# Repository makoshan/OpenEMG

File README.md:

# OpenEMG

**简体中文** · [English](README.en.md) · **[官网 openemg.org](https://openemg.org/)**

OpenEMG 是一个 **16 通道开源肌电手环**项目。我们想用腕部的表面肌电信号识别手势。桌面软件可以查看各通道波形、录制动作和训练模型。

我们想做肌电界的 DeepSeek。电路、结构、固件和桌面软件全部开源，谁都可以照着做一块板，用自己的数据训练模型。

OpenEMG 由人和 AI 共同研发。项目还在早期，电路、代码和文档里难免有错。如果你发现问题，欢迎[提 issue](https://github.com/makoshan/OpenEMG/issues)。如果你改好了代码、电路，或测出了不同的结果，也欢迎[提交 PR](https://github.com/makoshan/OpenEMG/pulls)，让其他人能复用你的工作。

**本次下单的最终主板为 OpenEMG MAIN V1.0B（2026-11-24）。** 首件已下单，实物待验。下载主板 PCB、五页原理图、Gerber 和实际贴片 BOM，见[主板定版资料](hardware/main-v1.0b/)。

[当前状态与进展计划](#当前状态与进展计划) · [Gallery](#gallery) · [工作原理与调研](#工作原理) · [桌面工作台](#桌面工作台)

| 正面 · U9 外壳与双板 | 贴肤面 · 金属电极触点 |
|---|---|
|  |  |

外观沿用 R13 表带，贴肤面按双 30 针电极软板布局绘制。长带 24 个、短带 4 个、主机底部 4 个圆形采样触点，共组成 16 对差分输入。底部另有 2 个方形辅助触点。这套组合尚待实物试装。 [表带模型](hardware/enclosure-46x40/c08b-shell-r13-notch/) · [双 30 针电极软板](hardware/16ch-u9-dual30/strap-fpc-30p/)

**OpenEMG 还在早期研制阶段。** 2026 年 11 月 15 日定下的是打样用的 PCB。固件、桌面软件与板子的联调、手势识别都还在开发，16 通道整机尚未上机验证。

> [!IMPORTANT]
> **人工审核准备下单 vs AI 生成未下单（硬件状态声明）**
> - **16 通道 `v0.01` 双板（人工工程师设计并逐脚审核通过 · 准备下单打样）**：[`hardware/16ch-afe-hirose-1mm-1nf/`](hardware/16ch-afe-hirose-1mm-1nf/) 中的 6 层主控板 `C08B-U9` 与 4 层采集板 `AFE-30P`（含 32 颗 `ESD401DPYR` 输入保护管、146 个贴片位号）由人工硬件工程师完成原理图与 PCB 布局布线，并对照 TI `ADS1298` 数据手册与 `SBAU171D` 评估板指南完成逐脚复核、DRC 与贴片极性核对，准备下单打样。
> - **其余衍生板卡、柔性软板与外壳（AI 生成设计 · 尚未人工审核 · 尚未下单）**：仓库内的 **2 通道 `ADS1292` 六触点板**、**8 通道 `D20-8CH` 腕带板**、**16 通道双 34 针（`D20/R4U6`）与广濑 `22 pF` 穿戴派生版（`16ch-u9-dual30`）**、**讯普 `2.0 mm` 对照版**、**全系柔性电极软板（FPC）** 以及 **全系 3D 打印外壳模型** 均由 AI 生成，尚未经过人工工程师逐板审核，也**尚未下单打样**（仅历史 8 路台架开发板 [`V12-R01`](hardware/8ch-ads1298/r01-bench/) 做过离体短接实板测试）。如需复刻 AI 生成的板卡，请务必在投产前自行人工复核原理图、封装手性与安全间距。

6 层主控板通过 20 针排线连接 4 层采集板。采集板用两颗 ADS1298，设计为 16 路差分输入。[打开人工审核双板工程与制造文件](hardware/16ch-afe-hirose-1mm-1nf/)

## Gallery

### PCB · 主控与采集板

**v0.01 的 PCB 设计已完成，下一步是打板、贴片和上电测试。** 采集板新增 32 颗输入保护管（D101–D132），贴片 BOM 和坐标表共 146 个位号。

| 板卡 | 正面 | 背面 |
|---|---|---|
| C08B-U9 主控板 |  |  |
| 16 通道采集板 |  |  |

图由同版 Gerber 生成。右列按翻到板背后的方向显示。[双板工程与制造文件](hardware/16ch-afe-hirose-1mm-1nf/) · [主控板元件正视图](hardware/renders/v001-mcu-front.png) · [采集板元件正视图](hardware/renders/v001-afe-front.png)

### 结构与装配

| v0.01 双板叠放 · 主控在上、采集在下 | U9 壳体与 v0.01 双板 · 分层视图 |
|---|---|
|  |  |

装配图按 v0.01 制造文件绘制，采用 0.8 mm 裸板。右图拉开了层间距，省略了元件、排线和电池。实物还没试装。[U9 外壳模型](hardware/16ch-u9-dual30/enclosure-u9-watch/) · [历代结构与表带图集](hardware/renders/)

### 走线与原理图

| C08B-U9 主控板 · 6 层铜箔 | 16 通道采集板 · 4 层铜箔 |
|---|---|
|  |  |

从左到右、从上到下依次是顶层、内层和底层。各层都从板顶看，方便对照走线和过孔。[主控 Gerber 与钻孔](hardware/16ch-afe-hirose-1mm-1nf/Gerber_C08B-U9_v0.01.zip) · [采集板 Gerber 与钻孔](hardware/16ch-afe-hirose-1mm-1nf/Gerber_AFE-30P.zip)

**[下载九页矢量原理图](hardware/16ch-afe-hirose-1mm-1nf/views/schematic.pdf)**。第 1 页是整机框图，第 2 页是电源树。第 3–7 页是主控板的供电、蓝牙、USB、板间接口与采样主控，第 8–9 页是采集板的模拟电源、采集芯片、电极接口与输入滤波。PDF 可放大和搜索位号；修改或联调电路请打开[嘉立创 EDA 专业版双板源工程](hardware/16ch-afe-hirose-1mm-1nf/OpenEMG_v0.01_DualBoard.epro2)或 [KiCad 8 原生双板与九页原理图工程](hardware/16ch-afe-hirose-1mm-1nf/kicad/)。

| 复刻资料 | 主控板 | 采集板 |
|---|---|---|
| 物料清单（BOM） | [主控 BOM](hardware/16ch-u9-dual30/fab-mcu-u9/jlc_smt_bom.csv) | [采集 BOM](hardware/16ch-afe-hirose-1mm-1nf/jlc_smt_bom.csv) |
| 贴片坐标（CPL） | [主控坐标](hardware/16ch-u9-dual30/fab-mcu-u9/jlc_smt_cpl.csv) | [采集坐标](hardware/16ch-afe-hirose-1mm-1nf/jlc_smt_cpl.csv) |

板厚、盘中孔工艺、钢网和底面贴装方向见[同版制造说明](hardware/16ch-afe-hirose-1mm-1nf/)。本版采集板用于离体台架，通电前请阅读[测试与佩戴边界](SAFETY.md)。

## 工作原理

捏指时，肌肉活动会让皮肤表面产生微小的电压变化。手环的每个通道测一对电极之间的电压差。电极位置不同，同一次捏指在各通道上录到的波形也不同。桌面软件把波形和动作标签一起保存，供模型学习区分放松、捏指等动作。

[查看同版九页原理图](hardware/16ch-afe-hirose-1mm-1nf/views/schematic.pdf)

摘下再戴，电极位置和松紧都会变。我们读过的一项四通道实验，在握拳、张手、屈腕和伸腕测试中判对了 152/160 次（95%），但论文没说明测试前是否重新佩戴，现有材料也不足以原样复现。[阅读项目调研节选与论文出处](research/wrist-semg.md)

结合文献复核与前期 8 路台架板（[`V12-R01`](hardware/8ch-ads1298/r01-bench/)）实测，定版电路与软件采用以下设计约束：

| 调研与实测维度 | 关键数据与来源 | 在 OpenEMG v0.01 与工作台中的落地 |
|---|---|---|
| **参考偏置与底噪** | `V12-R01` 实板短接输入底噪 **`2.8 µV`**，连续 10 分钟 **`1,187,774` 帧零丢包**；悬空不接参考电极上臂时 50 Hz 共模飙至 `10 mV` 饱和 | 盒底设独立 `BIAS / REF` 辅助触点，由 `U1` 单源经 `392 kΩ` 驱动偏置（`U2` 偏置输出悬空防双运放互顶），录制前先过 **5 秒静息信号体检**（`p95 > 150 µV` 阻断、`50 Hz` 能量占比 `> 40%` 提示重贴参考电极） |
| **双芯片同步与采样率** | 对照 ETH Zurich BioGAP-Ultra 双 `ADS1298` 架构与腕部 sEMG 有效频带（`20–450 Hz`） | 两颗 `ADS1298` 共用同一颗 `2.048 MHz` 有源晶振消除帧间漂移，硬件采样率定为 **`1000 SPS`**（兼容 `2000 SPS` 商用腕带回放与对比） |
| **跨佩戴特征与分类器** | 单次佩戴内准确率极易虚高；逐通道 z-score 标准化会抹掉空间幅值比，换位置重戴后性能骤降 | 禁用单通道标准化；提取 **`250 ms` 窗五频带对数功率（`bands5`：`20–45`、`55–95`、`105–145`、`155–245`、`255–445 Hz`）+ 收缩线性判别（Shrinkage LDA）**，桌面端强制按独立佩戴编号做**跨佩戴留一验证** |
| **人体供电互锁** | 市电 USB 直连存在故障漏电风险 | 主控板内建硬件互锁（检测 `VBUS` 自动拉高 `AFE_OE_N` 切断采集模拟电），`JP701` 默认空贴；桌面软件对未完成实物安全验收的 `c08b-16ch / 8ch / 2ch` 保持默认录制锁关闭（`record: false`） |

## 当前状态与进展计划

**2026-11-15 · 现在做到哪了**　16 通道 v0.01 的双板设计已定，工程、原理图、Gerber 和贴片文件已公开。固件通过了主机端测试，桌面工作台能演示 16 路波形。**这版整机还没有实测数据。最近的目标是让首板在台架上连续采到 16 路已知信号。**

#### 首板回来前

| 工作 | 还要做什么 |
|---|---|
| 打板与贴片 | 用 11 月 15 日定版包打样。核对板厚、盘中孔和钢网，在贴装预览里逐面检查两颗 ADS1298、三只排线座和 32 颗保护管。 |
| 固件适配 | [`c08b-bringup`](firmware/c08b-bringup/) 与 [`c08b-stream`](firmware/c08b-stream/) 已对照 `v0.01` 双板网表完成适配（双片独立 `INT_TEST=1` 测试源、`Pin 62 RLDIN=+2.5 V` 禁置 `RLD_MEAS/MUX=010`、`Pin 60 RLDREF=AGND` 禁置 `RLDREF_INT`，支持经蓝牙或 USB 接收器在线切换 `500/1000/2000 SPS` 及安全读写校验 `ADS1298` 寄存器，见[板间与传输协议说明](firmware/transport-protocol.md)），待回板后实机烧录验证。 |
| 测试准备 | 准备 20 针排线、转接线和离体信号源。把每个输入脚对应到桌面的 CH1–CH16，列好短接、已知信号和断流三组测试。 |

#### 样板到手后：先在台架测

| 工作 | 要拿到的结果 |
|---|---|
| 来板与供电 | 核对贴片方向、排线两端的 1 脚和通断。记录数字电源、正负模拟电源、基准电压、启动时序和纹波；验证 USB 插入时采集供电互锁。 |
| 双板通信 | 分别读回两颗 ADS1298 的 ID 和寄存器，观察各自的数据就绪信号，核对两组八路数据的顺序。 |
| 16 路模拟采集 | 先短接输入测各路底噪，再逐路注入已知信号。记录增益、极性、工频干扰和相邻通道串扰；用模拟负载检查偏置输出。 |
| 无线传输与桌面录制 | 真机连续传输，统计采样率、丢帧和延迟。用桌面端看波形、打标签、保存、关闭再回放；断连后检查文件是否完整、间断是否可见。2、8 通道另做兼容回归。 |
| 外壳、软板与电池 | 试装双板和电芯，实插 20 针板间排线和两条 30 针软尾。检查锁扣能否操作、合盖是否夹线，再测采集功耗、温升和续航。 |

#### 台架通过后：再做佩戴与手势验证

| 工作 | 怎样判断进展 |
|---|---|
| 佩戴前检查 | 核对贴肤触点、限流路径、电池供电与充电互锁，完成佩戴安全复核，再安排佩戴采集。[安全说明](SAFETY.md) |
| 电极接触与数据 | 记录佩戴位置和松紧，比较静息、动作、摘下重戴后的各路信号。保留动作标签和佩戴编号，找出容易失去接触的通道。 |
| 手势识别 | 先做放松、唤起和四向滑动六类。用一次佩戴训练，另一次佩戴测试；分别记录各类识别结果、响应时间和静息误触发。 |
| 开源复现 | 补齐装配照片、固件版本、桌面连接步骤和首板测试记录。让另一位开发者按公开文件从装配走到录制，记录卡在哪一步。 |

### 桌面工作台（支持 16 / 8 / 2 通道）

桌面工作台现已统一支持 **16 通道（OpenEMG 双 `ADS1298` · `1000 Hz`）**、**8 通道（唯理腕带 `2000 Hz` / OpenEMG 单 `ADS1298` `1000 Hz`）** 与 **2 通道（OpenEMG `ADS1292` · `1000 Hz`）**，顶部设备栏一键切换后自动匹配通道数、采样率、环形电极图、工程隔离目录与特征训练流水线。界面采用暖米色手帐实验台配色，录制前先过 5 秒静息信号体检（检查链全频段查 `50 Hz` 工频，显示链 `50 Hz` 陷波 + `20–450 Hz` 带通），内置跨佩戴留一评估与 3D 手势游戏《掌中天劫》。[打开软件目录与运行说明](app/)

| 16 通道肌电工作室（双 `ADS1298` · `16 CH · 1000 Hz`） | 8 通道校准采集中（满高八路滚动波形 · `8 CH · 2000 Hz`） |
|---|---|
|  |  |
| **2 通道入门工作台（`ADS1292` · `2 CH · 1000 Hz`）** | **跨佩戴评估剧场（重戴留一验证 `93%` + 学习曲线 + 聚类散点）** |
|  |  |
| **实时识别仪表盘（`0.65` 置信红线 + 放松底噪门控）** | **内置 3D 肌电实战游戏《掌中天劫》** |
|  |  |

图中 16 通道与 2 通道界面使用合成台架信号演示；在对应实板通过台架与佩戴安全验收前，软件默认保持硬件录制锁关闭（`record: false`）。

### 各版本工程与实测记录

目前优先打样并验证**人工审核通过的 16 通道 `v0.01` 双板**；其余 AI 生成的 16 / 8 / 2 通道衍生板、软板与外壳均尚未下单，进度与状态列在下表。

| 通道 | 硬件工程 | 固件 | 3D 外观（AI 生成 · 未下单） | 审核与下单实测状态 |
|---|---|---|---|---|
| **16 通道** | **[v0.01 双板与广濑 1 nF（人工审核）](hardware/16ch-afe-hirose-1mm-1nf/)** · **[A5＋B1 双层表带软板（已下单待试装）](hardware/16ch-afe-hirose-1mm-1nf/strap-fpc-a5b1/)** · [广濑 22 pF 穿戴版（AI）](hardware/16ch-u9-dual30/) · [讯普双 30 针（AI）](hardware/16ch-afe-xunpu-2mm-1nf/) · [双 34 针（AI）](hardware/16ch-c08b-round/) | [主控自检](firmware/c08b-bringup/) · [双 ADS1298 采集](firmware/c08b-stream/) | **[25 mm R3 外壳与 TPU 表带（含六孔修订底盖，已下单待试装）](hardware/16ch-afe-hirose-1mm-1nf/enclosure-25mm-r3/)** · [U9 广濑版手表壳](hardware/16ch-u9-dual30/enclosure-u9-watch/) · [双 30 针四层软板](hardware/16ch-u9-dual30/strap-fpc-30p/) | **`v0.01` 双板已由人工工程师逐脚审核通过；配套 `strap-fpc-a5b1` 双层软板与 `25 mm R3` 外壳/表带已投单打样**，待回件验证 16 路采集与断电试装。其余派生版尚未下单（讯普版另有[偏置待确认项](hardware/16ch-afe-xunpu-2mm-1nf/#待工程师确认)）。 |
| **8 通道** | [D20-8CH 腕带板（AI）](hardware/8ch-ads1298/afe-d20-8ch/) · [11 页原理图 PDF](hardware/8ch-ads1298/afe-d20-8ch/views/schematic.pdf) · [34P/20P 逐针核对表](hardware/8ch-ads1298/afe-d20-8ch/PINOUT-AND-REVIEW.md) · [R01 台架板（已实测）](hardware/8ch-ads1298/r01-bench/) | [腕带采集](firmware/c08b-stream/) · [R01 蓝牙采集](hardware/8ch-ads1298/r01-bench/firmware-f05-ble-dout/) | [R12 外壳](hardware/enclosure-46x40/c08b-shell-r12/) · [D2-8CH 电极软板](hardware/8ch-ads1298/strap-fpc-d2-8ch/) | `R01` 历史台架实板短接输入采集 10 分钟，`1,187,774` 帧序号连续、底噪 `2.8 µV`。`D20-8CH` 腕带板已整理 11 页全套原理图、34P/20P 逐针表与排线朝向图，**待人工工程师独立审板**，尚未下单。 |
| **2 通道** | [ADS1292 六触点板（AI）](hardware/2ch-ads1292/) · [双肩外接线 S1 与整板 STEP](hardware/2ch-shoulder-s1/) · [3 页原理图 PDF](hardware/2ch-ads1292/views/schematic.pdf) · [六触点极性核对表](hardware/2ch-ads1292/PINOUT-AND-REVIEW.md) | [XIAO 蓝牙采集](firmware/xiao-ads1292-2ch/) | [R7 六触点外壳](hardware/enclosure-46x40/ads1292-shell-r7/) | 已整理 3 页原理图、六触点贴肤翻面/元件面极性对照与 8 测点表（自动 DRC 与逐脚对板已过），**待人工工程师独立审板**，尚未下单。 |

## 开始使用

[官网 openemg.org](https://openemg.org/) · [桌面工作台](app/) · [软件与开发环境](firmware/software.md) · [板间与传输协议](firmware/transport-protocol.md) · [硬件与制造文件索引](hardware/README.md) · [通电与佩戴安全须知](SAFETY.md)

[软件许可 MIT](LICENSE) · [硬件许可 CERN-OHL-S-2.0](LICENSE-HARDWARE) · [第三方声明](THIRD_PARTY_NOTICES.md)

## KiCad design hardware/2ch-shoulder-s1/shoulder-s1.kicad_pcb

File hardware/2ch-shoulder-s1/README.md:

# S1 双肩肌电采集板

S1 是从双通道 R10派生的台架候选。使用 ADS1292 与原有 P44e + XIAO nRF52840 Sense。43.1 × 36.5 × 0.8 mm 四层采集板底面有两只电极线插座。工程入口为 [shoulder-s1.kicad_pro](shoulder-s1.kicad_pro)。静态设计已完成，尚未打样、上电或贴肤。

[下载整板 STEP](shoulder-s1.step) · [KiCad 原理图](shoulder-s1.kicad_sch) · [接口针序与出线图](board-bottom.png) · [模型来源与许可](MODELS.md)

## 两束电极线

| 插座 | 出线方向（从元件面看） | 1 脚 | 2 脚 | 3 脚 |
|---|---|---|---|---|
| J3 LEFT | 西边 | 左肩 CH1+ | 左辅助参考 | 左肩 CH1− |
| J4 RIGHT | 东边 | 右肩 CH2+ | 右辅助参考 | 右肩 CH2− |

每束使用一只 JST PHR-3 线端胶壳配 S3B-PH-SM4-TB 板端侧插座。线端按壳体的 1 脚标记核序，通断档逐芯核对。每束两根测量线在同侧成对走线，第 2 脚单独引出。两根辅助参考分别经过 620 kΩ，在板内汇合后经 300 kΩ 接 RLDOUT；它们由同一偏置驱动，均不可接屏蔽或电源地。四个信号输入各经两颗 300 kΩ 和中间节点的 ESD 保护。两只插座的 MP 是机械焊脚，每只座的两只 MP 在板上相连并与信号、电源地隔开。[JST PH 系列图纸](https://www.jst-mfg.com/product/pdf/eng/ePH.pdf)

J3 与 J4 的插拔轴线分别朝外，PCB 面内出口各自面向就近板边。两座均增加板底高度。肩颈壳需要双侧开口和两处夹持绝缘外皮的线夹，导线拉力应由壳体承受。既有腕带底盖开的是六个干电极孔，不能据此认定新插头能穿壳。首件需核插头、线夹、完整插拔行程及右侧上下两层 JST 线束与 J2 排线的共存。板底插座可手焊用于首件。

## 台架验收设计

下表为建议的原型验收条件，全部未实测。使用模拟负载和隔离差分信号源，记录实际线长、输入幅值、增益与原始帧。上电前核回路和电池供电时序；保留 R32 / Q1 的 USB 关断互锁及固件硬件锁。未确认供电、互锁及限流前，保持锁定。

| 测项 | 方法 | 建议通过条件 |
|---|---|---|
| 线束与保护 | 断电，从每根线远端量到板端针脚。核 4 个测量输入各到第一、第二级电阻末端，参考线到 RLDOUT。 | 线序同上表，输入约 300 / 600 kΩ，参考各约 920 kΩ。检查压接和绝缘。 |
| 通道与频响 | 正常双差分输入模式，先给左路、再给右路，从线束远端注入等幅正弦，另一通道接匹配的无信号模拟负载。每路扫 20、50、100、250、450 Hz。禁用显示端滤波，用原始 SPI 采样比较幅值。 | 4 kHz 为首选档。两路单独核算相对 100 Hz 的增益，各频点在 ±3 dB 内。记录另一通道同频响应和底噪，建议串扰 ≤ −40 dB。 |
| 同步和掉样 | 分别以 2 kHz、4 kHz 连续采 60 秒，同步比对 DRDY 边沿、两通道原始帧和溢出计数。 | 每个 DRDY 对应一个含两路数据的帧。按实测时钟核采样频率，完整记录窗口内无跳帧、无溢出。分别记录 SPI 与主机收包结果。 |
| 外接线与互锁 | 接上预定长度线束，测双路输入短接底噪、工频拾取及 RLD 是否振荡。用模拟负载验证 USB 插入后 TP8 拉低并停止转换；再用断电样件检查壳体夹线和插拔。 | 留存波形、互锁电平、端口及线束照片。人体试用另行做安全复核。 |

芯片的 2 / 4 kSPS 档 −3 dB 带宽分别为 524 / 1048 Hz。板级频响还受输入电路与线束影响。[TI 数据手册](https://www.ti.com/lit/ds/symlink/ads1292.pdf)

## 复核

在本目录用 KiCad 10.0.6 和 Python 3 运行 `python3 verify.py`。它从 S1 原理图重新导出网表，与从 R10 原理图导出的固定对照表 `r10-pins.csv` 比较，核对两组线序、其余 R10 引脚和关键保护件的标称值，注入右肩反接反例，再检查 ERC、重铺铜 DRC、未连接和图板一致性。工程带有 0.45 mm 无限流输入铜到电源和数字网络的间距规则。外壳、实际线缆和寄生参数仍须实测。

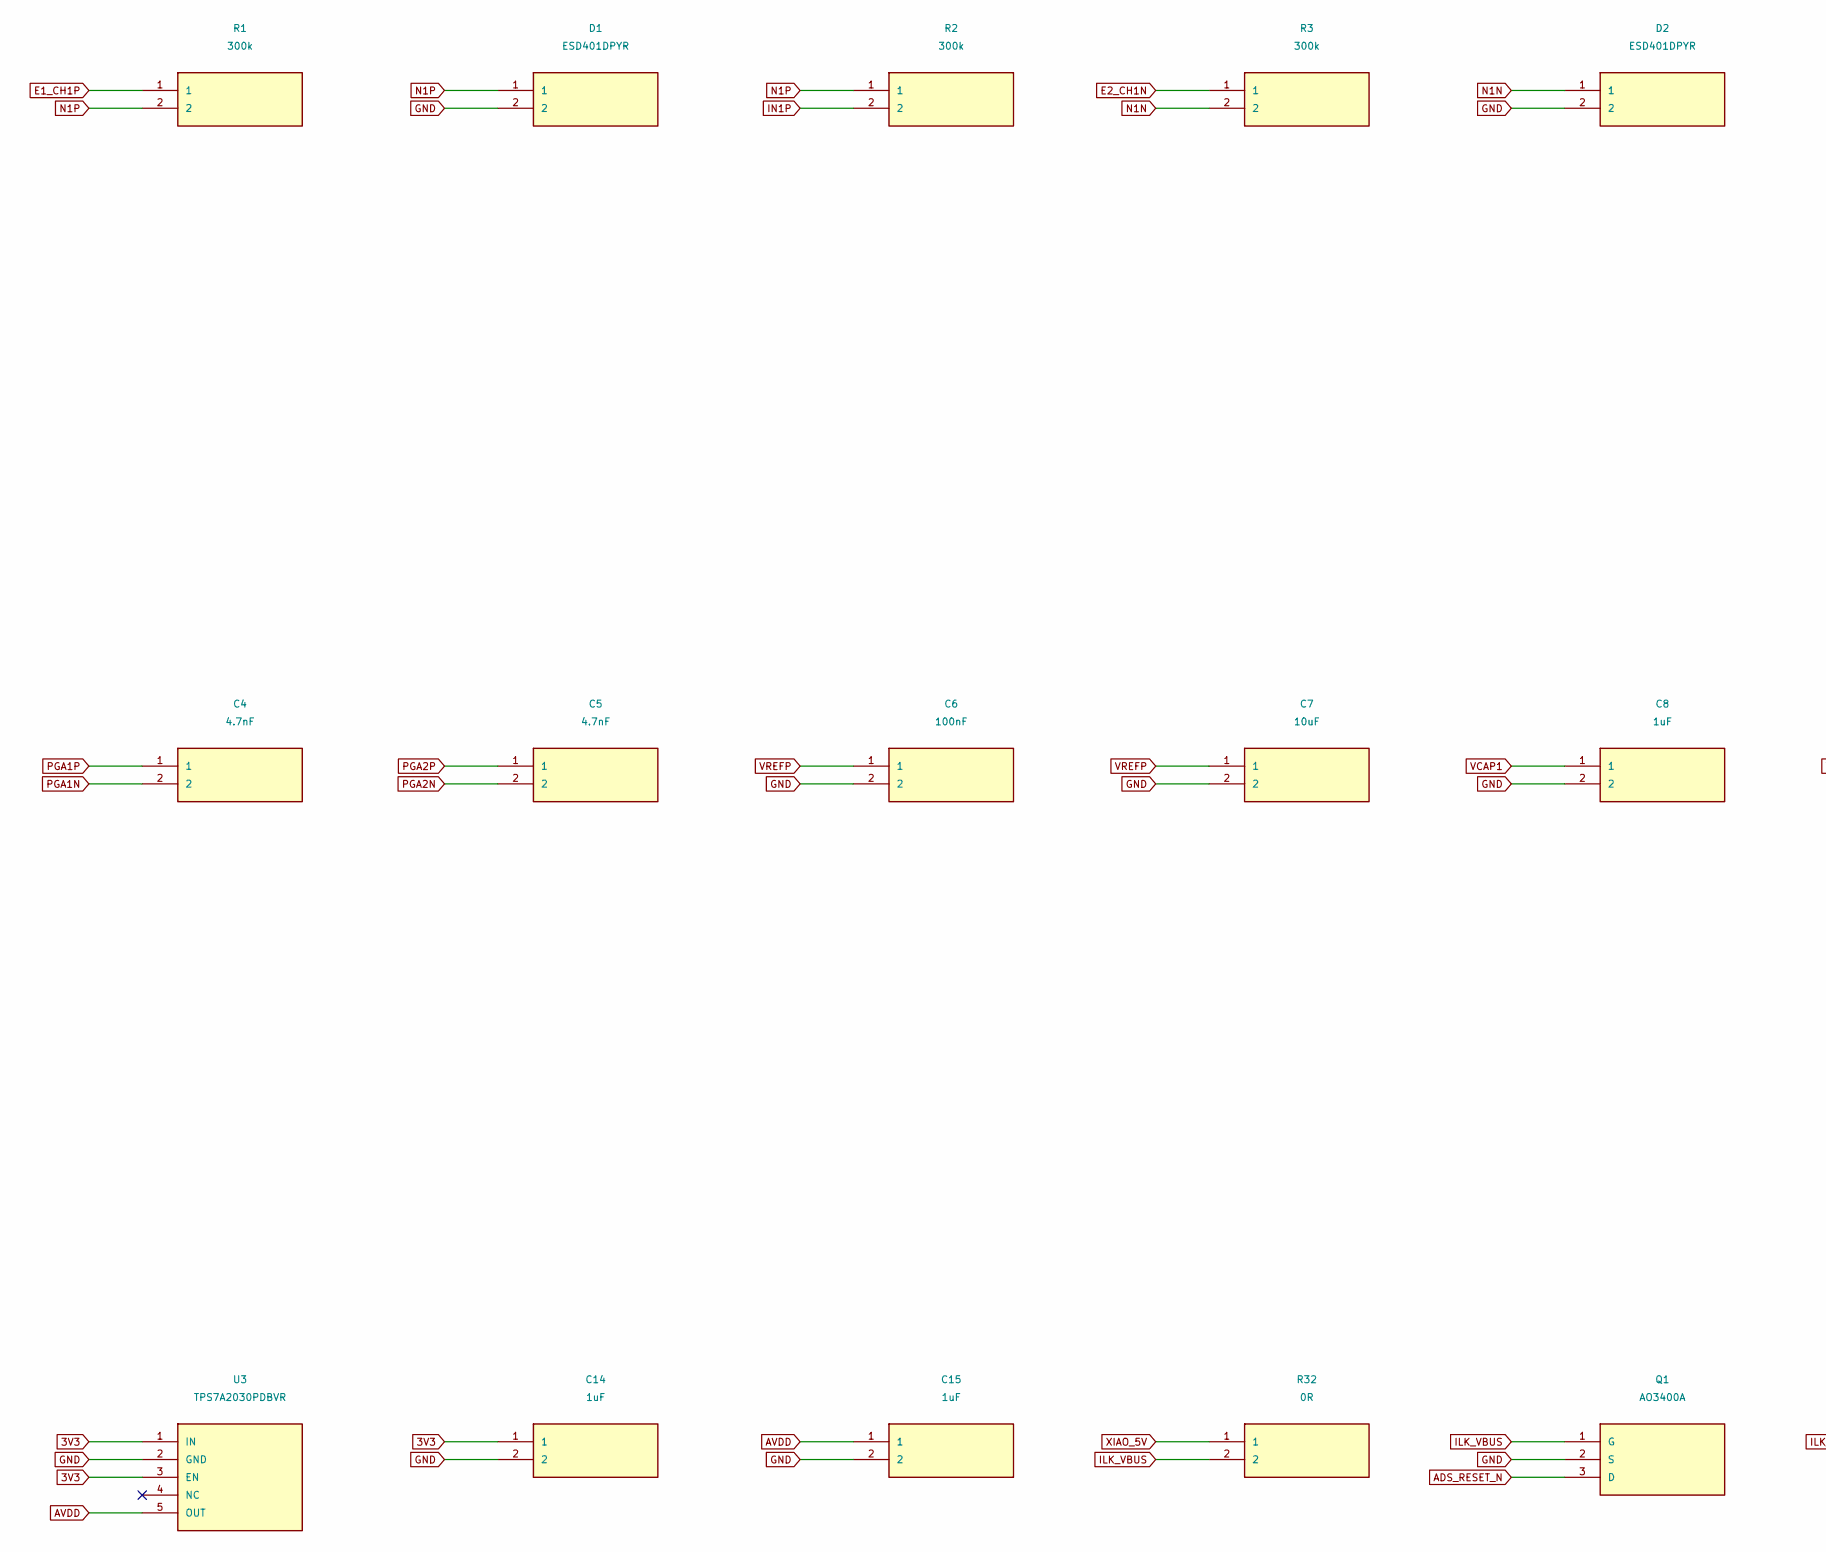
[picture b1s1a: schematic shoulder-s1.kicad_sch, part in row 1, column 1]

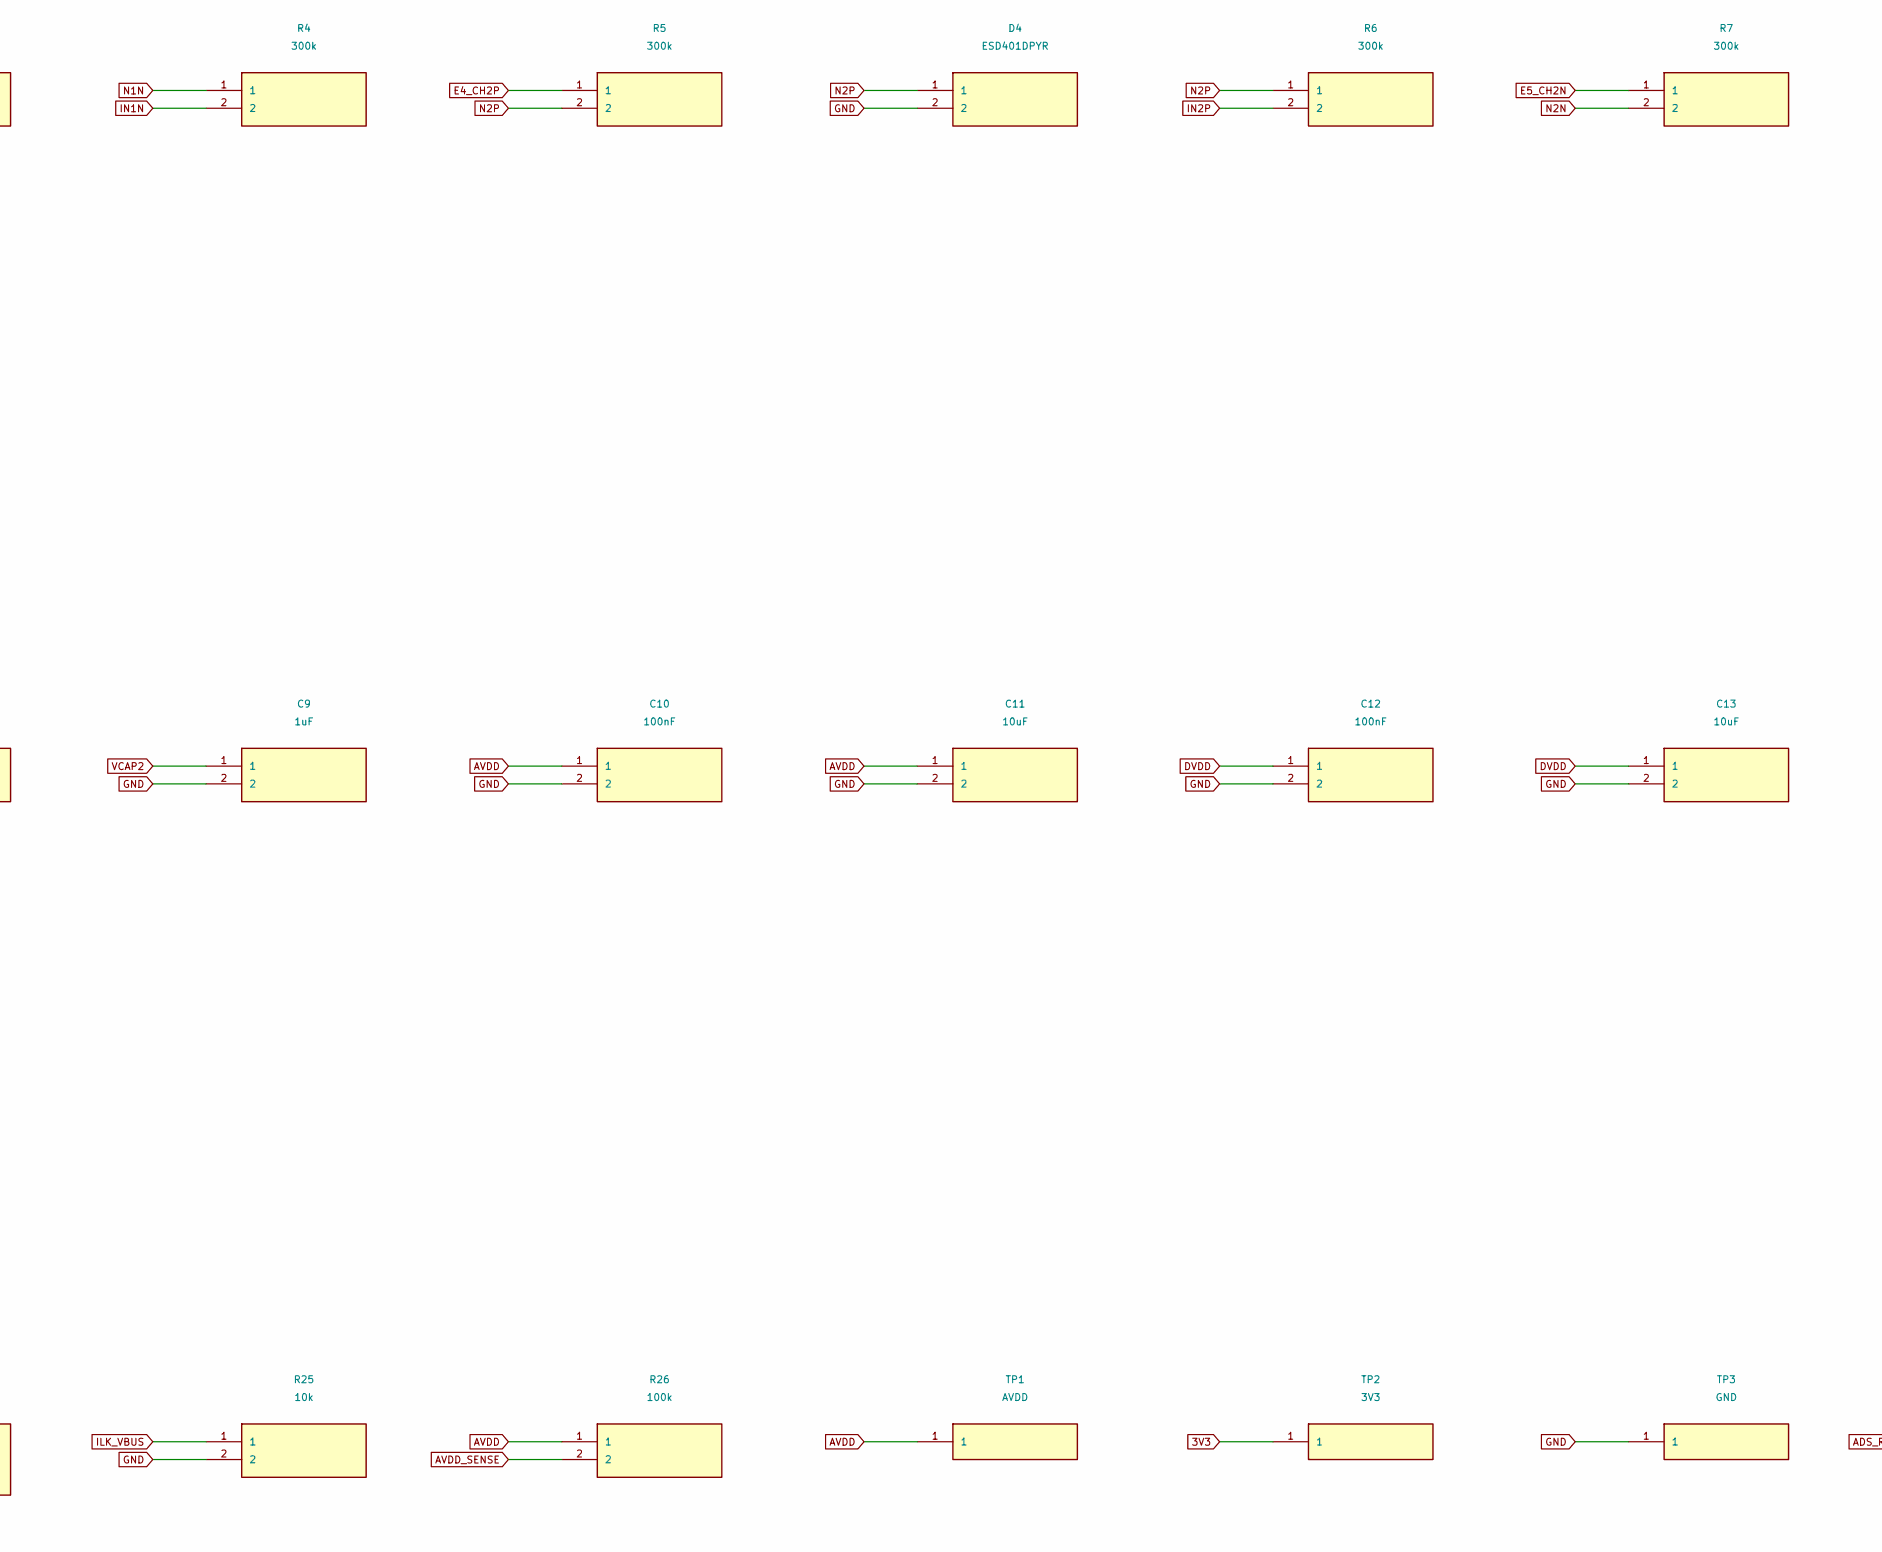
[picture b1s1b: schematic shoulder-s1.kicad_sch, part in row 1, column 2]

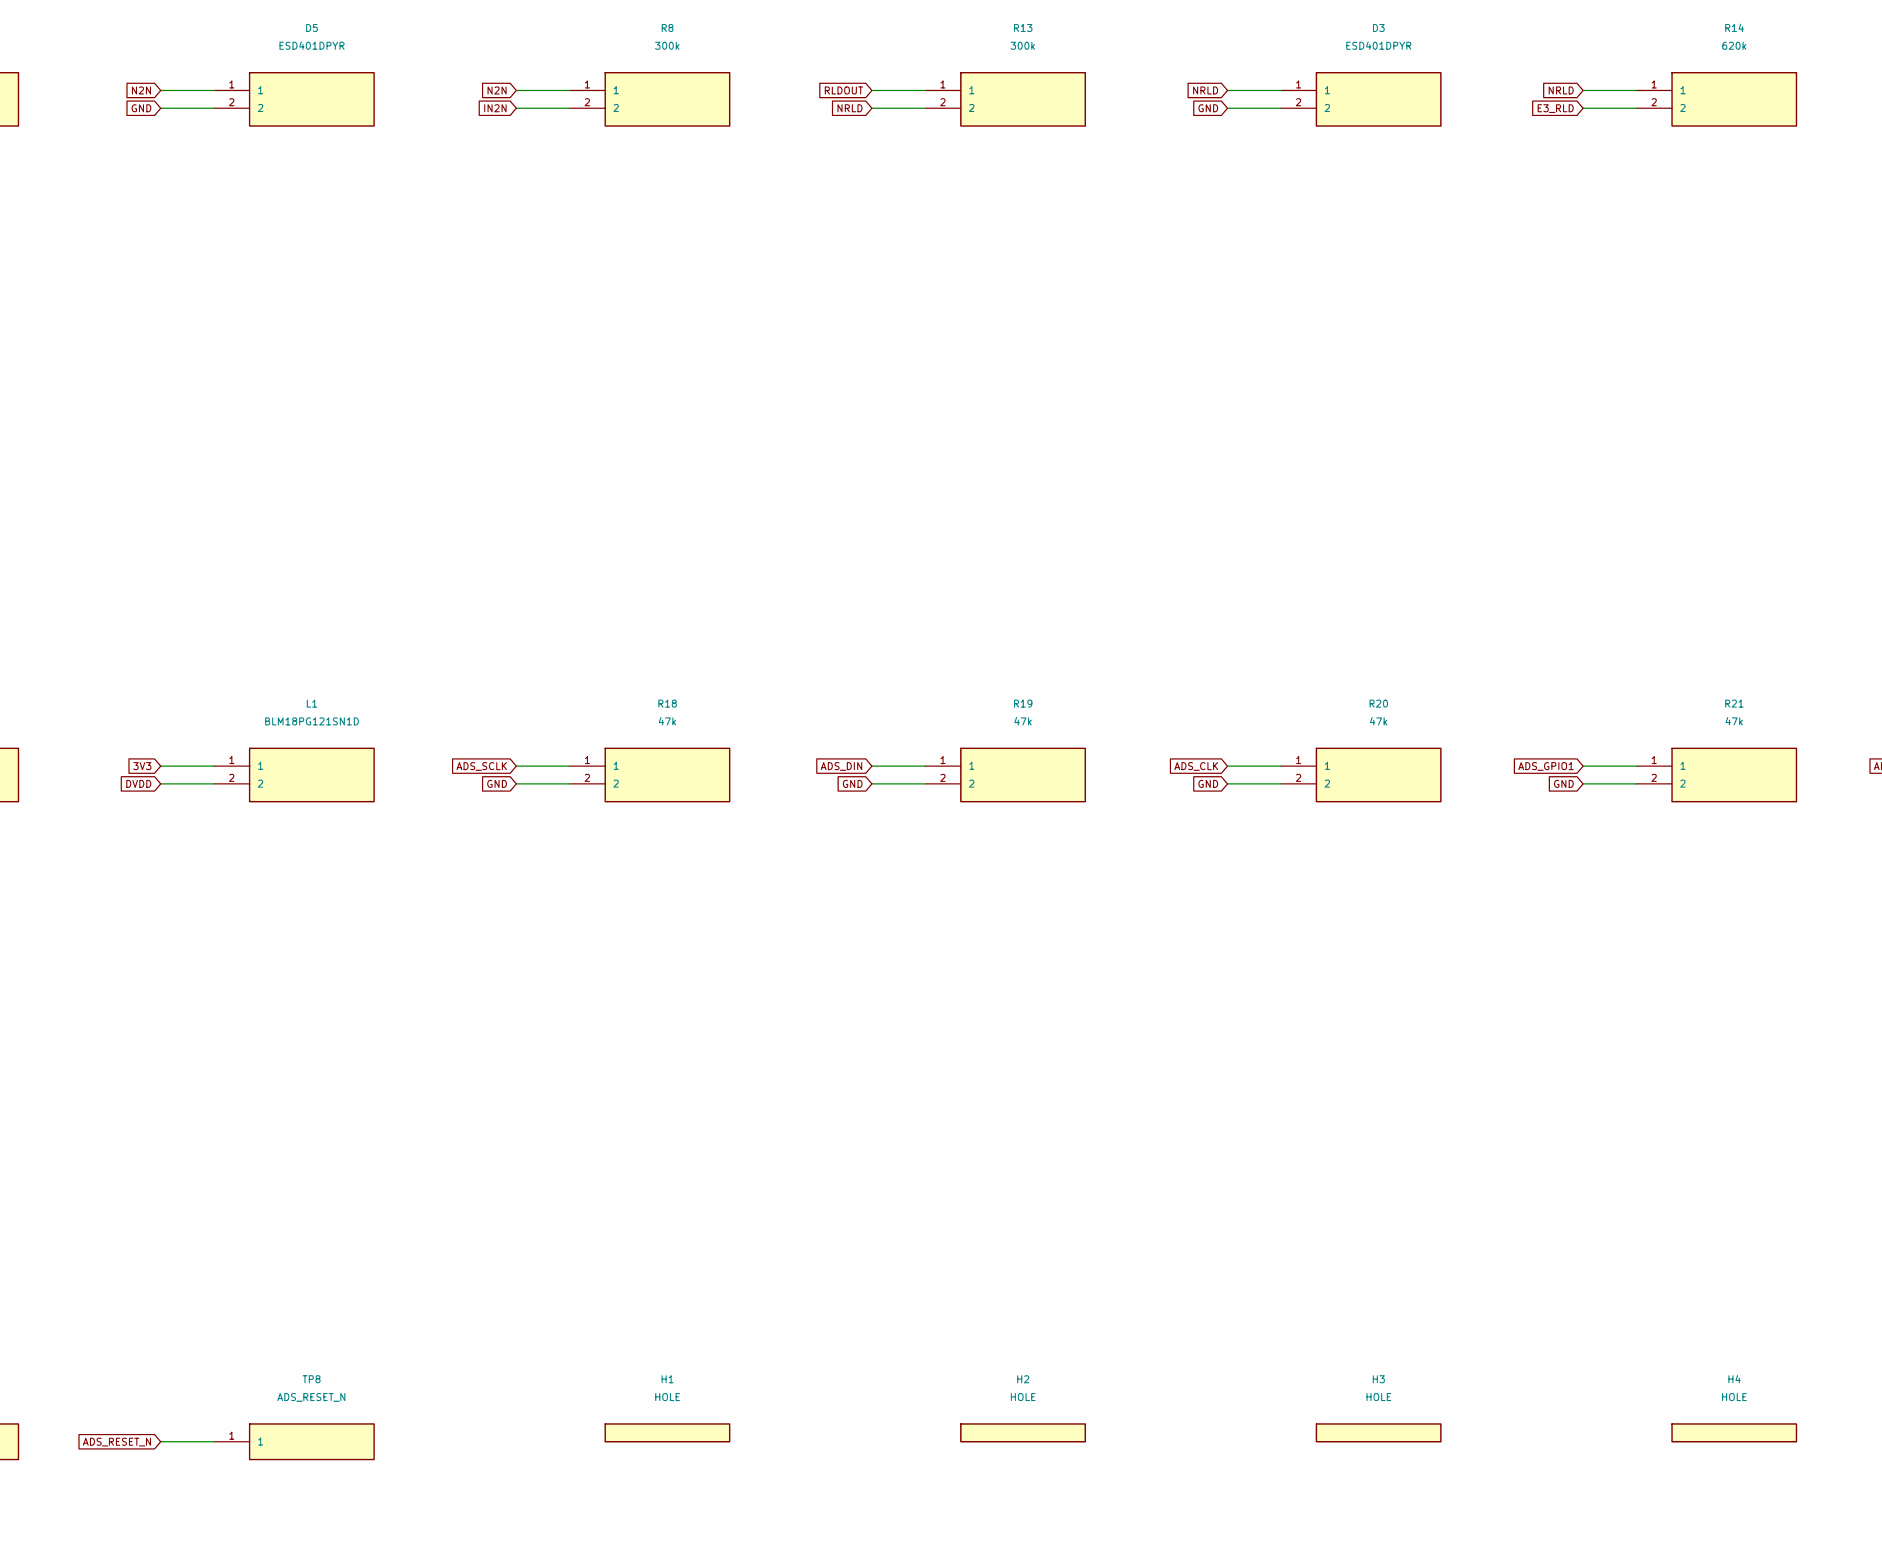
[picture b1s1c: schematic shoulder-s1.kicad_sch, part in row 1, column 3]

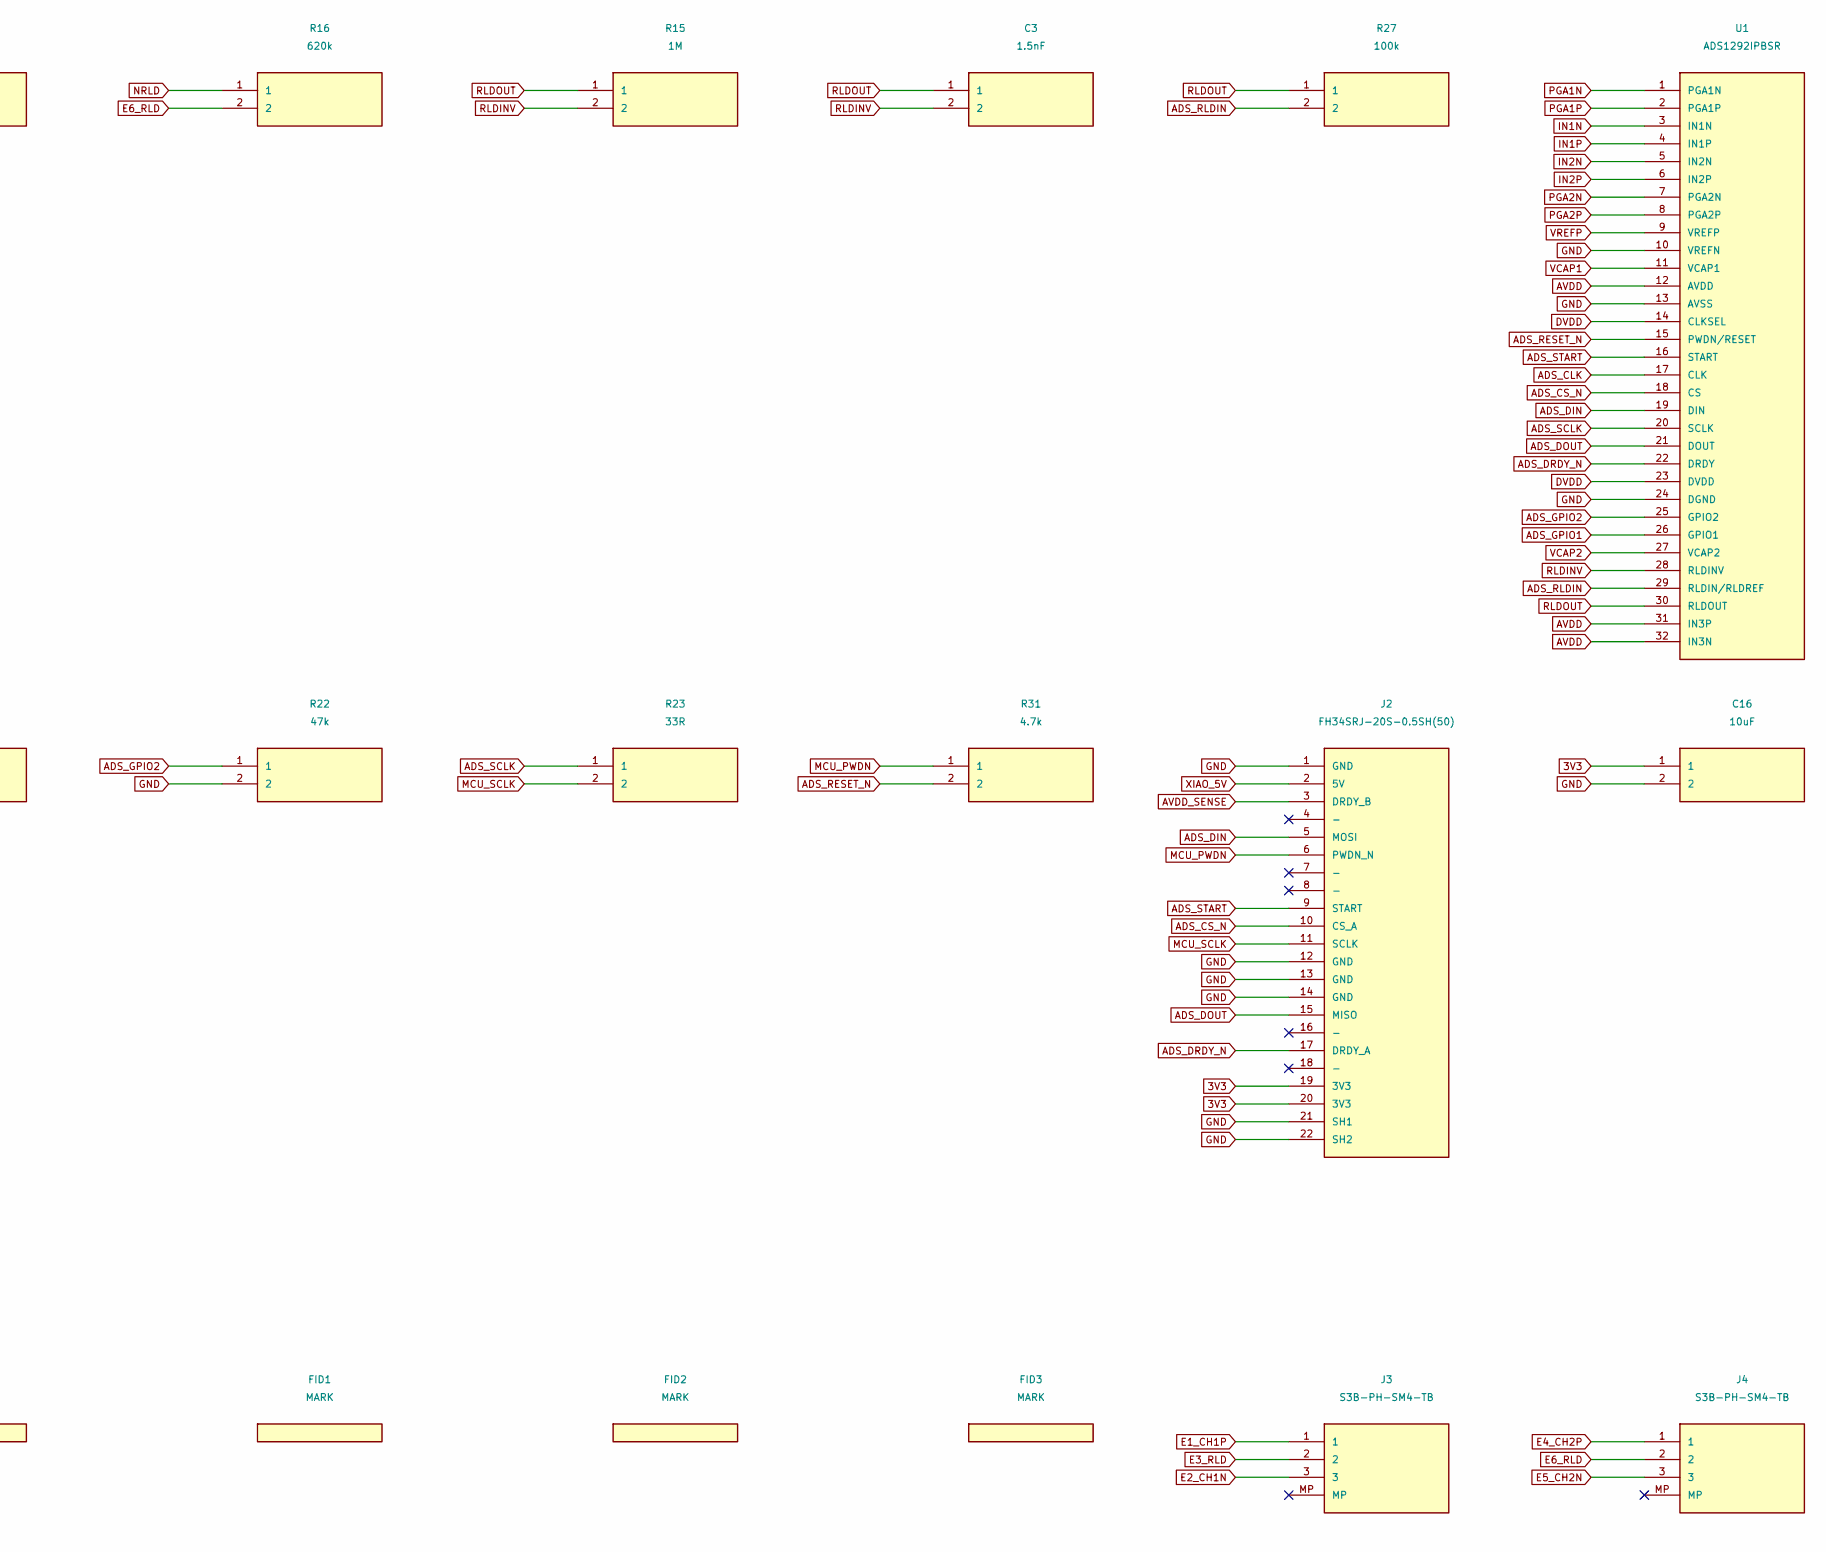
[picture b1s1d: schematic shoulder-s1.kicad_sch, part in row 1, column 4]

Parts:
C3: 1.5nF; C_0402_1005Metric; LCSC C52037853
C4, C5: 4.7nF; C_0402_1005Metric; LCSC C1518204
C6, C10, C12: 100nF; C_0402_1005Metric; LCSC C1525
C7, C16: 10uF; C_0603_1608Metric; LCSC C19702
C8, C9, C14, C15: 1uF; C_0402_1005Metric; LCSC C52923
C11, C13: 10uF; C_0402_1005Metric; LCSC C15525
D1, D2, D3, D4, D5: ESD401DPYR; Texas_DPY0002A_0.6x1mm_P0.65mm; LCSC C1974752
FID1, FID2, FID3: MARK; Fiducial_1mm_Mask2mm
H1, H2, H3, H4: HOLE; HOLE_1P7
J2: FH34SRJ-20S-0.5SH(50); Hirose_FH34SRJ-20S-0.5SH; LCSC C2802370
J3, J4: S3B-PH-SM4-TB; JST_PH_S3B-PH-SM4-TB_1x03-1MP_P2.00mm_Horizontal
L1: BLM18PG121SN1D; L_0603_1608Metric; LCSC C14709
Q1: AO3400A; SOT-23; LCSC C20917
R1, R3, R5, R7, R13: 300k; R_0603_1608Metric; LCSC C23024
R2, R4, R6, R8: 300k; R_0402_1005Metric; LCSC C25774
R14, R16: 620k; R_0603_1608Metric; LCSC C23219
R15: 1M; R_0402_1005Metric; LCSC C26083
R18, R19, R20, R21, R22: 47k; R_0402_1005Metric; LCSC C25792
R23: 33R; R_0402_1005Metric; LCSC C25105
R25: 10k; R_0402_1005Metric; LCSC C25744
R26, R27: 100k; R_0402_1005Metric; LCSC C25741
R31: 4.7k; R_0402_1005Metric; LCSC C25900
R32: 0R; R_0402_1005Metric; LCSC C17168
TP1: AVDD; TestPoint_Pad_D1.0mm
TP2: 3V3; TestPoint_Pad_D1.0mm
TP3: GND; TestPoint_Pad_D1.0mm
TP8: ADS_RESET_N; TestPoint_Pad_D1.0mm
U1: ADS1292IPBSR; TQFP-32_5x5mm_P0.5mm; LCSC C2651570
U3: TPS7A2030PDBVR; SOT-23-5; LCSC C963429

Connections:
3V3: C14.1, C16.1, J2.19 (3V3), J2.20 (3V3), L1.1, TP2.1, U3.1 (IN), U3.3 (EN)
ADS_CLK: R20.1, U1.17 (CLK)
ADS_CS_N: J2.10 (CS_A), U1.18 (CS)
ADS_DIN: J2.5 (MOSI), R19.1, U1.19 (DIN)
ADS_DOUT: J2.15 (MISO), U1.21 (DOUT)
ADS_DRDY_N: J2.17 (DRDY_A), U1.22 (DRDY)
ADS_GPIO1: R21.1, U1.26 (GPIO1)
ADS_GPIO2: R22.1, U1.25 (GPIO2)
ADS_RESET_N: Q1.3 (D), R31.2, TP8.1, U1.15 (PWDN/RESET)
ADS_RLDIN: R27.2, U1.29 (RLDIN/RLDREF)
ADS_SCLK: R18.1, R23.1, U1.20 (SCLK)
ADS_START: J2.9 (START), U1.16 (START)
AVDD: C10.1, C11.1, C15.1, R26.1, TP1.1, U1.12 (AVDD), U1.31 (IN3P), U1.32 (IN3N), U3.5 (OUT)
AVDD_SENSE: J2.3 (DRDY_B), R26.2
DVDD: C12.1, C13.1, L1.2, U1.14 (CLKSEL), U1.23 (DVDD)
E1_CH1P: J3.1, R1.1
E2_CH1N: J3.3, R3.1
E3_RLD: J3.2, R14.2
E4_CH2P: J4.1, R5.1
E5_CH2N: J4.3, R7.1
E6_RLD: J4.2, R16.2
GND: C6.2, C7.2, C8.2, C9.2, C10.2, C11.2, C12.2, C13.2, C14.2, C15.2, C16.2, D1.2, D2.2, D3.2, D4.2, D5.2, J2.1 (GND), J2.12 (GND), J2.13 (GND), J2.14 (GND), J2.21 (SH1), J2.22 (SH2), Q1.2 (S), R18.2, R19.2, R20.2, R21.2, R22.2, R25.2, TP3.1, U1.10 (VREFN), U1.13 (AVSS), U1.24 (DGND), U3.2 (GND)
ILK_VBUS: Q1.1 (G), R25.1, R32.2
IN1N: R4.2, U1.3 (IN1N)
IN1P: R2.2, U1.4 (IN1P)
IN2N: R8.2, U1.5 (IN2N)
IN2P: R6.2, U1.6 (IN2P)
MCU_PWDN: J2.6 (PWDN_N), R31.1
MCU_SCLK: J2.11 (SCLK), R23.2
N1N: D2.1, R3.2, R4.1
N1P: D1.1, R1.2, R2.1
N2N: D5.1, R7.2, R8.1
N2P: D4.1, R5.2, R6.1
NRLD: D3.1, R13.2, R14.1, R16.1
PGA1N: C4.2, U1.1 (PGA1N)
PGA1P: C4.1, U1.2 (PGA1P)
PGA2N: C5.2, U1.7 (PGA2N)
PGA2P: C5.1, U1.8 (PGA2P)
RLDINV: C3.2, R15.2, U1.28 (RLDINV)
RLDOUT: C3.1, R13.1, R15.1, R27.1, U1.30 (RLDOUT)
VCAP1: C8.1, U1.11 (VCAP1)
VCAP2: C9.1, U1.27 (VCAP2)
VREFP: C6.1, C7.1, U1.9 (VREFP)
XIAO_5V: J2.2 (5V), R32.1

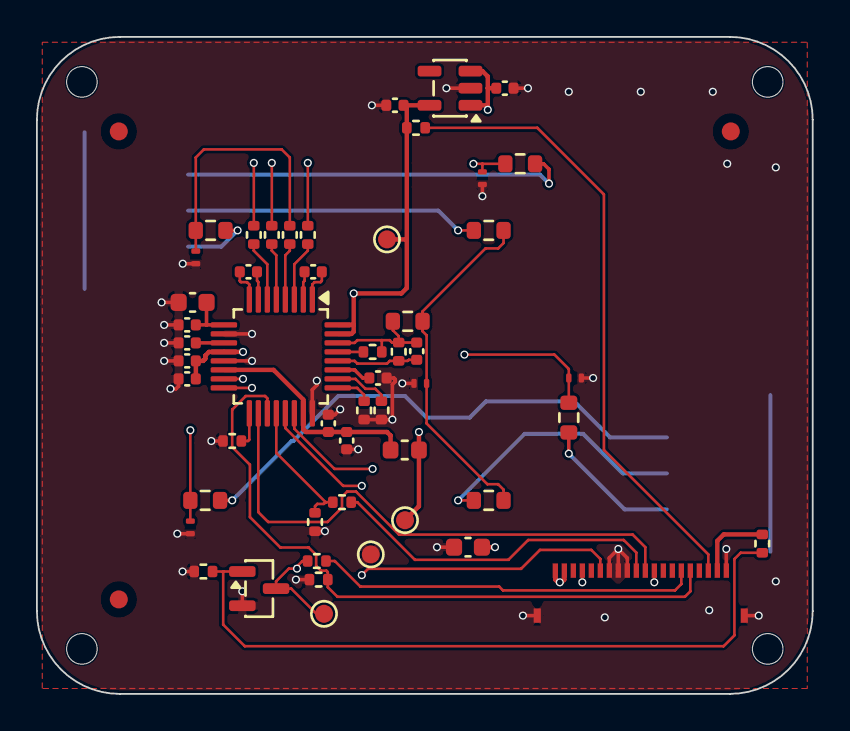
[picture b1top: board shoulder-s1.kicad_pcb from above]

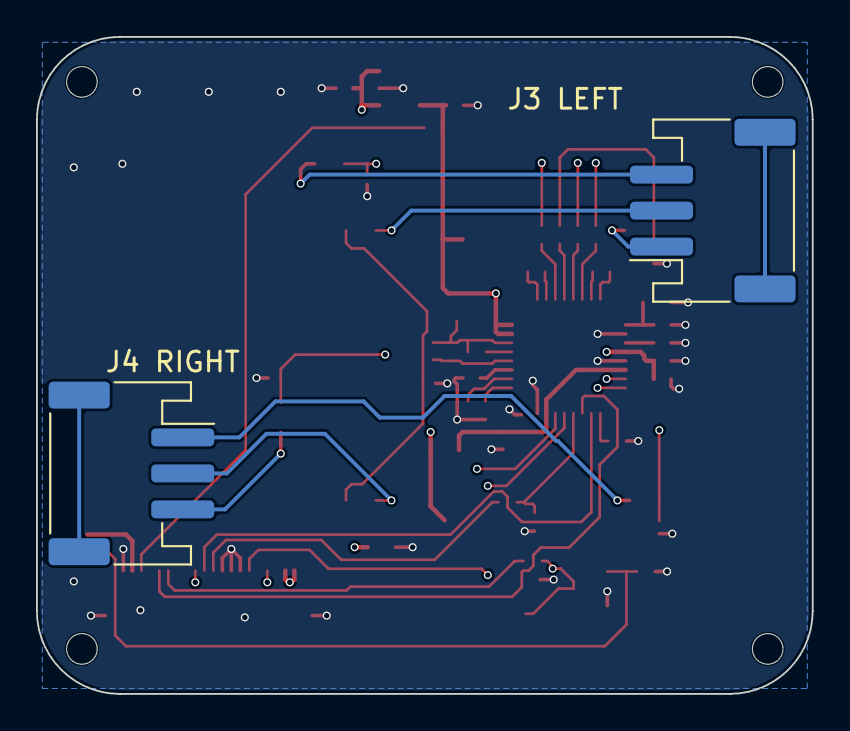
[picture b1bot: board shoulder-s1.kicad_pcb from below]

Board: 4 copper layers, 43.1 x 36.5 mm, 60 parts (2 on the bottom side), 44 nets.
